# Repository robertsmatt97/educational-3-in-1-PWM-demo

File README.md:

# educational-3-in-1-PWM-demo
Fall 2019 Power Electronics: Modern Topics Semester Project (with Houshang Salimian Rizi)   
EE 394 Semester Project, assigned by Dr. Alex Hanson   

## Description
The 3-in-1 PWM Converter is used as a visual aid for students to learn about designing basic PWM converters, including the Buck, Boost, and Buck-Boost topologies.   
The converter was designed using KiCAD, with the specifications located in `Project_1.pdf`.   
Instructions on how to use the converter, as well as design choices and improvements, can be found in `User_Manual.pdf`.

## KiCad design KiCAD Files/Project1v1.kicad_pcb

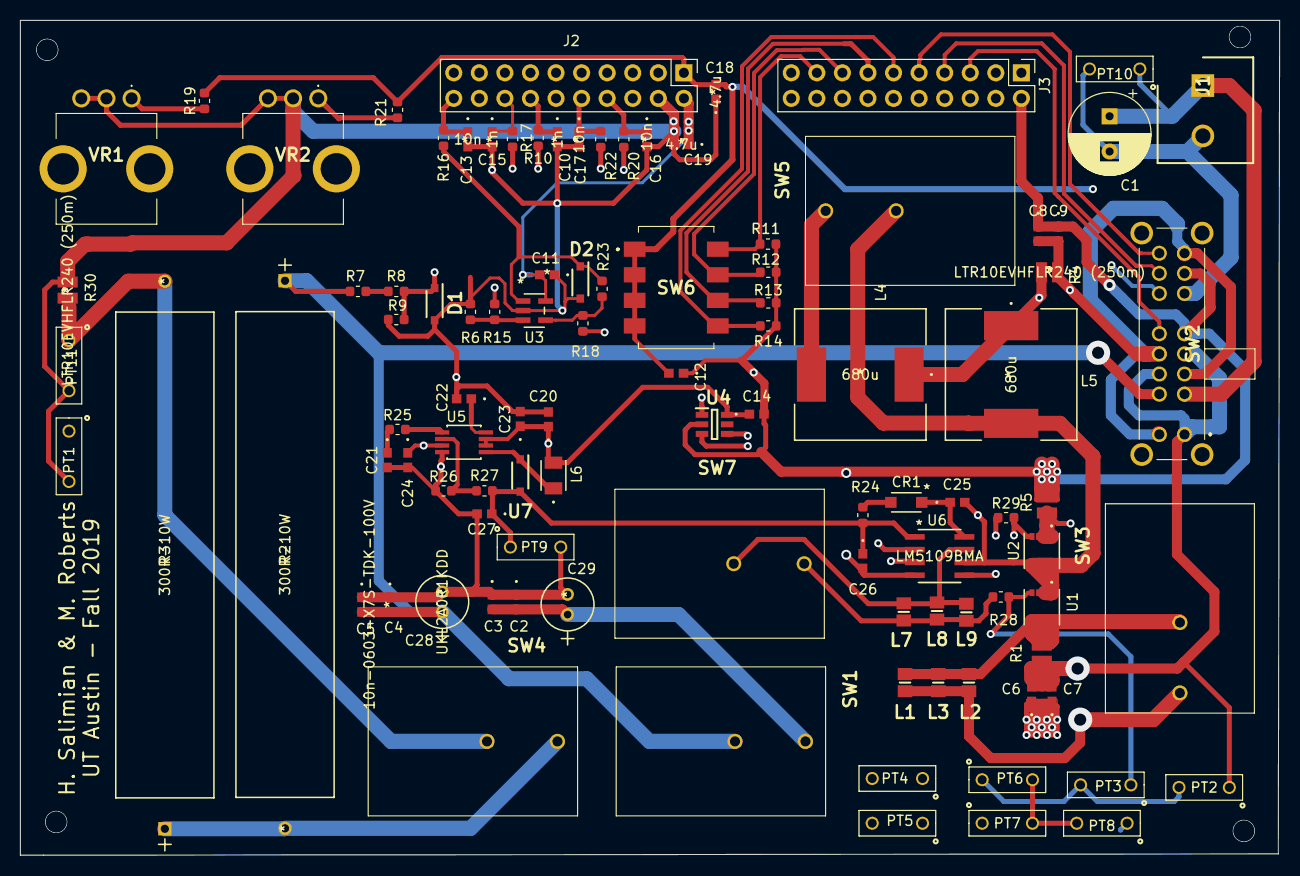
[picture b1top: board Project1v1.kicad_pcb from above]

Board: 4 copper layers, 125.1 x 82.9 mm, 101 parts (0 on the bottom side), 52 nets.

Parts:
C1: UBT2A100MPD8TD; CP_Radial_D8.0mm_P3.50mm
C2, C3, C4, C5, C6, C7, C8, C9: 10n-0603-X7S-TDK-100V; AMK107BBJ476MA-RE
C10, C15: 1n; AMK107BBJ476MA-RE
C11, C22: 100n; AMK107BBJ476MA-RE
C12, C14, C24: 1u; AMK107BBJ476MA-RE
C13, C16, C17: 10n; AMK107BBJ476MA-RE
C18, C19, C20, C27: 4.7u; AMK107BBJ476MA-RE
C21: 1.6n; AMK107BBJ476MA-RE
C23: 1u - 25 V; AMK107BBJ476MA-RE
C25: 0.1u; AMK107BBJ476MA-RE
C26: AMK107BBJ476MA-RE
C28, C29: UKL2A0R1KDD
CR1: MBR1H100SFT3G
D1, D2: D_Zener; SODFL3516X120N
J1: OSTTA020161; SHDR2W130P0X500_1X2_1000X900X1290P
J2: J5_J7; PinHeader_2x10_P2.54mm_Top_Bottom_Vertical
J3: J6_J8; PinHeader_2x10_P2.54mm_Top_Bottom_Vertical
L1, L2, L3: 1n; INDC2012X105N
L4, L5: 680u; SRR1260-100M
L6: CVH252009-4R7M
L7, L8, L9: 100n; INDC2012X105N
PT1, PT2, PT3, PT4, PT5, PT6, PT7, PT8, PT9, PT10, PT11: Probe_test
R1, R4, R5, R30: LTR10EVHFLR240 (250m); LTR10EVHFLR240
R2, R3: 300R-10W; SQP10AJB-300R
R6, R7, R8, R9, R23: 4.7k-1%; R_0603_1608Metric
R10, R16, R17: 10k; R_0603_1608Metric
R11, R12, R13, R14, R19, R20, R21, R22: 47k; R_0603_1608Metric
R15, R18: 56k-1%; R_0603_1608Metric
R24, R28, R29: 2R; R_0603_1608Metric
R25: 27k; R_0603_1608Metric
R26: 18k; R_0603_1608Metric
R27: 158k; R_0603_1608Metric
SW1, SW3, SW4, SW5, SW7: R1966ABLKBLKEF
SW2: EG4319
SW6: ADE04S04
U1, U2: CSD19538Q3AT
U3: OPA325xxDBV; OPA320SAIDBVT
U4: LMP8640HVMK-H_NOPB; SOT95P280X110-6N
U5: TPS61085TDGKR
U6: LM5109BMA
U7: PMEG2010AEH; SODFL3516X120N
VR1, VR2: PTV09A-4020U-B103; PTV09A4015FB103

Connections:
+3V3: C12.2, C18.2, J2.1, R19.2, R21.2, SW2.14, SW6.1, SW6.3, SW6.5, SW6.7
+5V: C11.2, C14.1, C19.1, C20.1, C23.1, C24.1, J2.11, L6.2, U3.5, U4.6, U5.3, U5.6, U5.7
+12V: C26.1, C27.1, PT9.1, R24.1, R27.2, U6.1, U7.2
B+: C1.1, J1.1, PT10.1, R15.2, SW2.2
B-: C1.2, J1.2, PT10.2, R18.2, SW2.6
Boost: J3.4, SW2.15
Buck: J3.3, SW2.13
Buck_Boost: J3.5, SW2.16
C1: C6.2, C7.2, PT2.1, R1.1, SW2.1, SW2.4, SW2.11
C2: C8.2, C9.2, PT4.2, PT5.2, R4.1, SW2.3, SW2.8, SW2.9, SW2.12, U4.4
C3: C2.1, C3.1, C4.1, C5.1, C6.1, C7.1, C8.1, C9.1, C10.2, C11.1, C12.1, C13.2, C14.2, C15.2, C16.2, C17.2, C18.1, C19.2, C20.2, C21.2, C22.2, C23.2, C24.2, C26.2, C27.2, C28.2, C29.2, D1.2, D2.2, J2.12, J3.11, PT1.2, PT6.2, PT7.2, PT8.2, PT9.2, PT11.2, R5.2, R6.1, R9.2, R11.1, R12.1, R13.1, R14.1, R26.1, R30.2, SW2.5, SW2.7, U3.2, U4.2, U5.4, U6.4, VR1.2, VR1.3, VR2.2, VR2.3
CCM-DCM: J3.6, R14.2, SW6.8
Duty_Cycle_Knob: C17.1, J2.15, R22.1
Freq-Sweep: J3.7, R13.2, SW6.6
Freq_Knob: C16.1, J2.14, R20.1
I_ind_p: L4.1, L5.1, PT5.1, R4.2, U4.3
I_switch: PT8.1, R5.1, U2.1, U2.2, U2.3
I_switch_meas: C15.1, J2.18, R17.1
unnamed: C2.2, C3.2, C29.1, SW1.2
unnamed: C21.1, R25.1
unnamed: C22.1, U5.8
unnamed: C25.1, CR1.1, U6.8
unnamed: CR1.2, R24.2
unnamed: D1.1, R8.1, R9.1, R10.2
unnamed: D2.1, R16.2, R23.1, U3.1
unnamed: L1.1, L2.1, L3.1, R1.2, SW3.1, U1.5, U1.6, U1.7, U1.8
unnamed: L4.2, SW5.2
unnamed: L6.1, U5.5, U7.1
unnamed: L7.1, L8.1, L9.1, R28.1, SW7.2
unnamed: PT11.1, R3.2, R30.1, SW4.1
unnamed: R2.2, R3.1, SW4.2
unnamed: R7.1, R8.2
unnamed: R6.2, R15.1, U3.3
unnamed: R17.2, U4.1
unnamed: R18.1, R23.2, U3.4
unnamed: R19.1, R20.2, VR1.1
unnamed: R21.1, R22.2, VR2.1
unnamed: R25.2, U5.1
unnamed: R26.2, R27.1, U5.2
OL-CL: J3.8, R12.2, SW6.4
Preset: J3.9, R11.2, SW6.2
R+: C4.2, C5.2, C28.1, PT1.1, R2.1, R7.2, SW1.1, SW2.10
S1: PT3.1, R28.2, U1.4
S2: PT7.1, R29.2, U2.4
Signal1: J3.1, U6.2
Signal2: J3.2, U6.3
Switch_Node: C25.2, L5.2, PT2.2, PT3.2, PT4.1, PT6.1, SW5.1, U1.1, U1.2, U1.3, U2.5, U2.6, U2.7, U2.8, U6.6
Vin_meas: C13.1, J2.20, R16.1
Vout_meas: C10.1, J2.17, R10.1
gate1: L7.2, L8.2, L9.2, SW7.1, U6.7
gate2: R29.1, U6.5
wire1-: L1.2, L2.2, L3.2, SW3.2

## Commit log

2021-01-31 Initial File Upload

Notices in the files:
parts and their libraries:
Copyright 2016 Accelerated Designs. All rights reserved.
